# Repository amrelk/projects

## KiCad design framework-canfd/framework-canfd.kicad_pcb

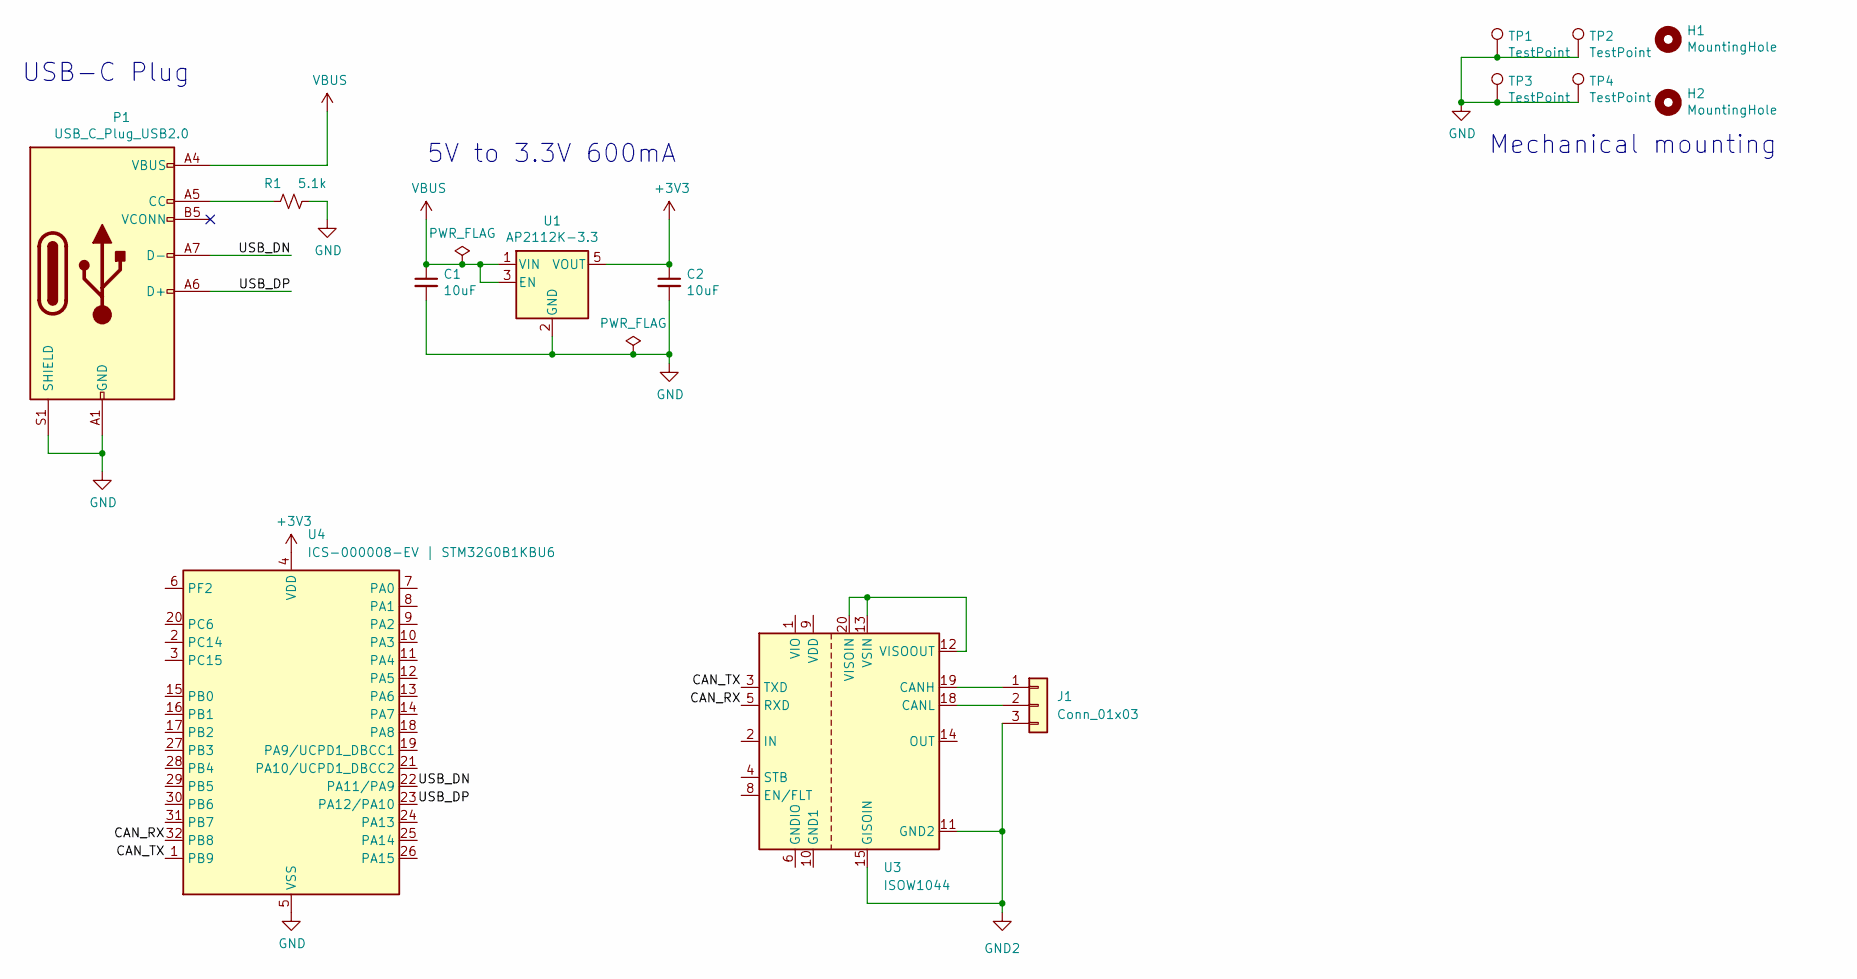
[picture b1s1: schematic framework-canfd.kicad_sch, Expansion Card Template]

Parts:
C1, C2: 10uF; C_0805_2012Metric
H1, H2: MountingHole; MountingHole_2.2mm_M2
J1: Conn_01x03; JST_GH_SM03B-GHS-TB_1x03-1MP_P1.25mm_Horizontal
P1: USB_C_Plug_USB2.0; USB_C_Plug_Molex_105444
R1: 5.1k; R_0603_1608Metric
TP1, TP2, TP3, TP4: TestPoint; TestPoint_Pad_1.5x1.5mm
U1: AP2112K-3.3; SOT-23-5
U3: ISOW1044; SOIC-20W_7.5x12.8mm_P1.27mm
U4: ICS-000008-EV | STM32G0B1KBU6; QFN-32-1EP_5x5mm_P0.5mm_EP3.45x3.45mm

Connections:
+3V3: C2.1, U1.5 (VOUT), U4.4 (VDD); also elsewhere on the board
/CAN_RX: U3.5 (RXD), U4.32 (PB8); also elsewhere on the board
/CAN_TX: U3.3 (TXD), U4.1 (PB9); also elsewhere on the board
/USB_DN: P1.A7 (D-), U4.22 (PA11/PA9); also elsewhere on the board
/USB_DP: P1.A6 (D+), U4.23 (PA12/PA10); also elsewhere on the board
GND: C1.2, C2.2, P1.A1 (GND), P1.A12 (GND), P1.B1 (GND), P1.B12 (GND), P1.S1 (SHIELD), R1.2, TP1.1, TP2.1, TP3.1, TP4.1, U1.2 (GND), U4.5 (VSS), U4.33 (VSS); also elsewhere on the board
GND2: J1.3, U3.11 (GND2), U3.15 (GISOIN), U3.16 (GISOIN), U3.17 (GISOIN)
unnamed: J1.1, U3.19 (CANH)
unnamed: J1.2, U3.18 (CANL)
unnamed: P1.A5 (CC), R1.1
unnamed: U3.12 (VISOOUT), U3.13 (VSIN), U3.20 (VISOIN)
VBUS: C1.1, P1.A4 (VBUS), P1.A9 (VBUS), P1.B4 (VBUS), P1.B9 (VBUS), U1.1 (VIN), U1.3 (EN)

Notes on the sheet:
USB-C Plug
5V to 3.3V 600mA
Mechanical mounting

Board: 2 copper layers, 14 parts (4 on the bottom side), 12 nets, no tracks yet.

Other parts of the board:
U2: STM32G0B1KBUx; QFN-32-1EP_5x5mm_P0.5mm_EP3.45x3.45mm

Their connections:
+3V3: U2.4 (VDD); also elsewhere on the board
/CAN_RX: U2.32 (PB8); also elsewhere on the board
/CAN_TX: U2.1 (PB9); also elsewhere on the board
/USB_DN: U2.22 (PA11/PA9); also elsewhere on the board
/USB_DP: U2.23 (PA12/PA10); also elsewhere on the board
GND: U2.5 (VSS), U2.33 (VSS); also elsewhere on the board

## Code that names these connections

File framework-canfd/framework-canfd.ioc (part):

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Mcu.Name=STM32G0B1K(B-C-E)Ux
Mcu.Package=UFQFPN32
Mcu.UserName=STM32G0B1KBUx
PA11\ [PA9].Mode=Device
PA11\ [PA9].Signal=USB_DM
PA12\ [PA10].Mode=Device
PA12\ [PA10].Signal=USB_DP
PB8.Mode=FDCAN_Activate
PB8.Signal=FDCAN1_RX
PB9.Mode=FDCAN_Activate
PB9.Signal=FDCAN1_TX
RCC.HSE_VALUE=8000000
RCC.SYSCLKFreq_VALUE=16000000
board=custom

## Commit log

2024-05-03 initial commit with ev24 common and a22verter
2024-05-06 first rev of cubemx genfile caching
2024-05-06 added basic workflow
2024-06-01 added httplib
2024-07-21 added framework canfd project and changed some code stuff
2024-07-26 started redoing evelinverter
2026-01-16 Update mkstm

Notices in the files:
framework-canfd/framework-canfd.kicad_pcb:
This work is licensed under a Creative Commons Attribution 4.0 International License
